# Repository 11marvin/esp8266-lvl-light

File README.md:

# ESP8266 LVL Light Control Board

This project contains the KiCad design files for a replacement control board used to control the LVL ceiling light (https://templates.blakadder.com/lvl_300.html) with additional features such as brightness adjustment, colour temperature control (CCT) and Wi-Fi connectivity. The board also includes provisions for connecting an I2C bus, a GPIO and power supply (3V3, GND).

## Features

- Control LVL ceiling light using ESP8266-12F
- Adjust brightness and color temperature (CCT)
- Wi-Fi connectivity for remote control and automation
- I2C bus and GPIO for additional device integration

## Board

32 mm x 20 mm (without antenna overlap)

### Front

### Back

## Contributing

Contributions are welcome! If you find any issues or have suggestions for improvements, please open an issue or submit a pull request.

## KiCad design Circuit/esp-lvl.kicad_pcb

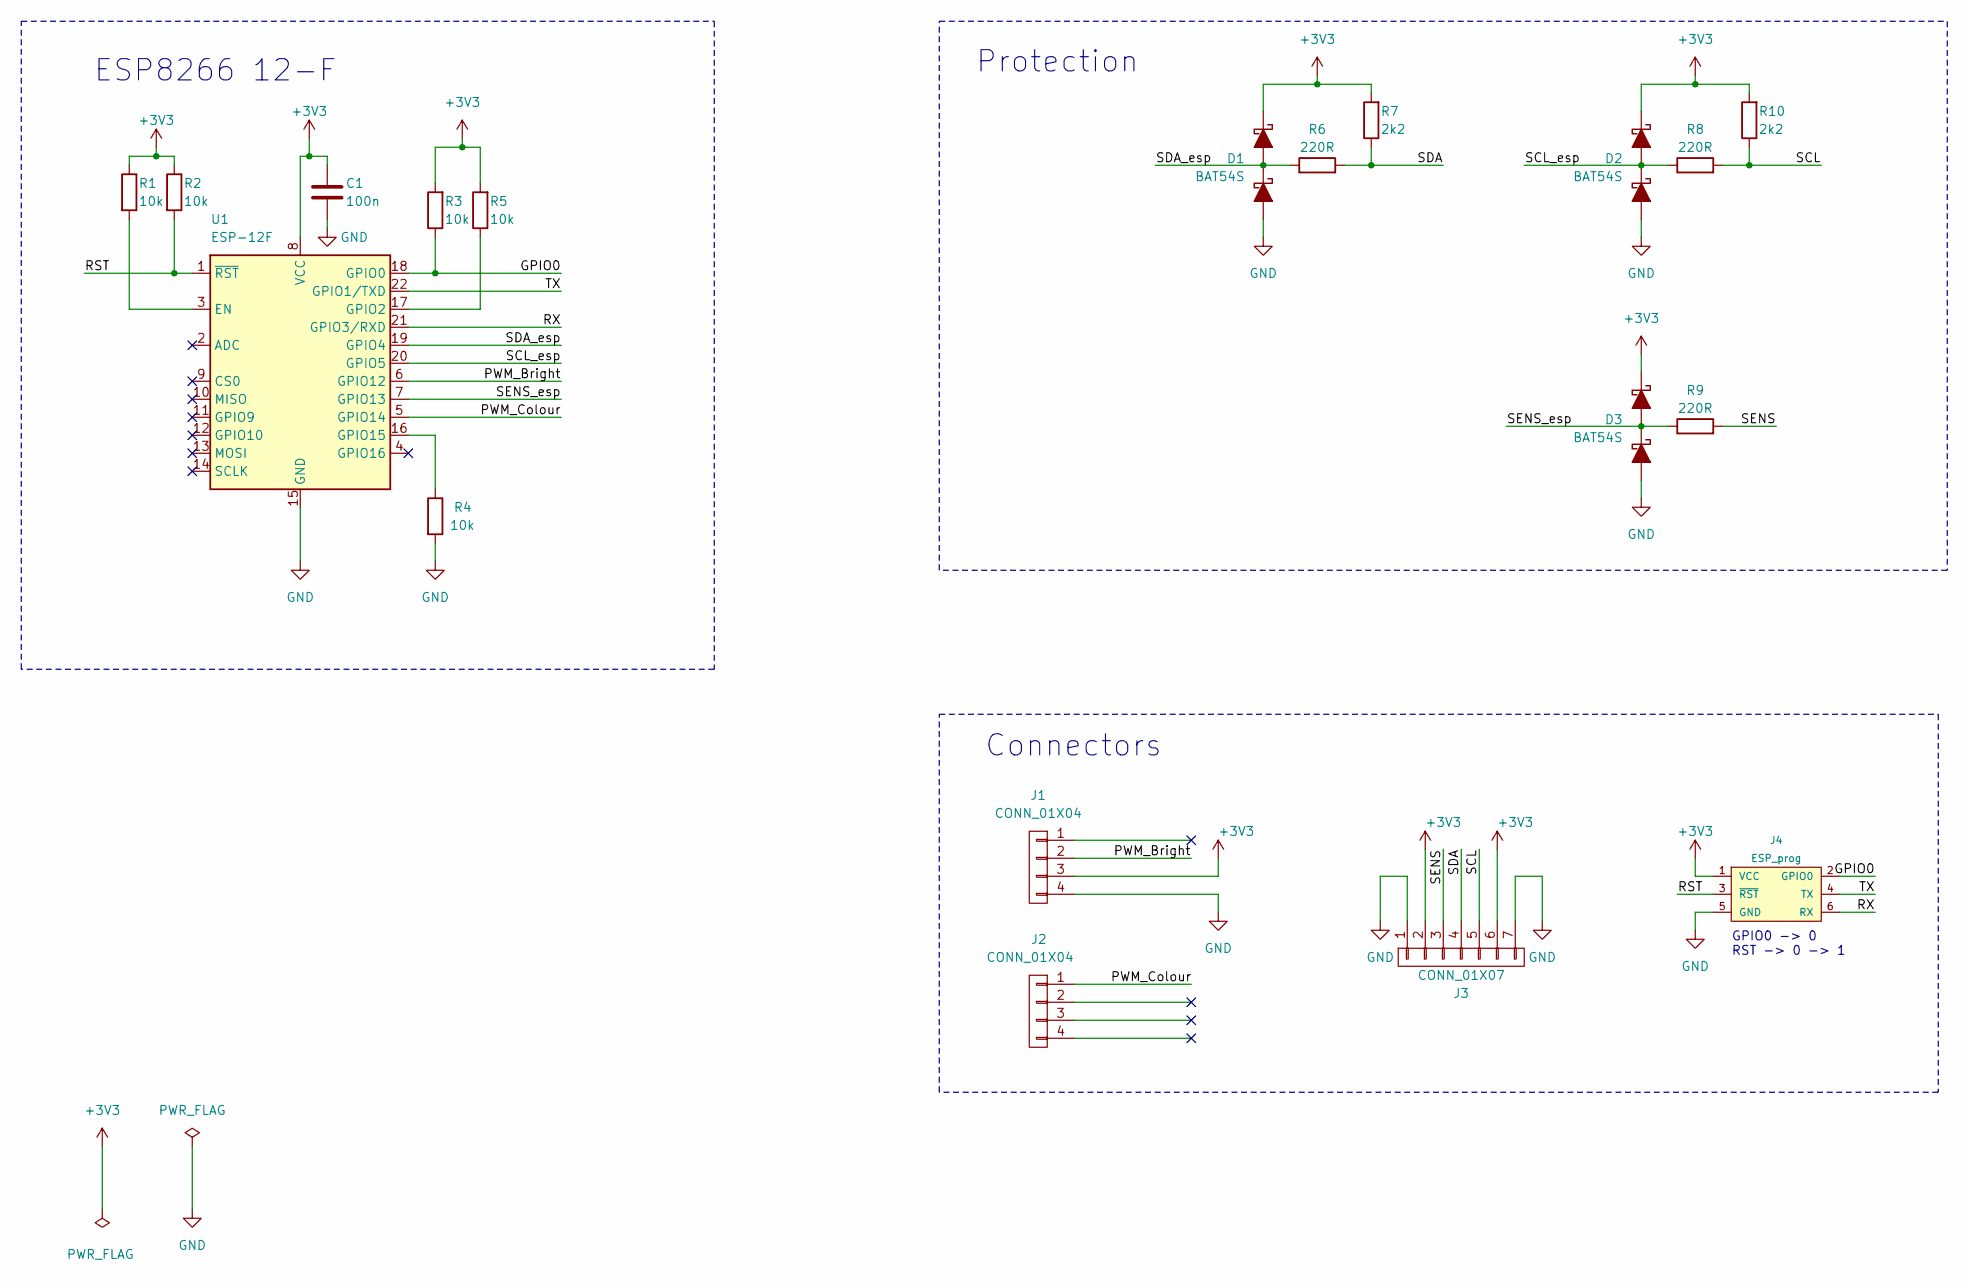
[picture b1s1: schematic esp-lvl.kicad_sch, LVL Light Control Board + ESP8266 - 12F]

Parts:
C1: 100n; C_0603_1608Metric
D1, D2, D3: BAT54S; SOT-23
J1, J2: CONN_01X04; PinHeader_1x04_P2.54mm_Vertical
J3: CONN_01X07; PinHeader_1x07_P2.54mm_Vertical
J4: ESP_prog; Tag-Connect_TC2030-IDC-NL
R1, R2, R3, R4, R5: 10k; R_0603_1608Metric
R6, R8, R9: 220R; R_0603_1608Metric
R7, R10: 2k2; R_0603_1608Metric
U1: ESP-12F; ESP-12E

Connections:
+3V3: C1.1, D1.2 (C), D2.2 (C), D3.2 (C), J1.3, J3.2, J3.6, J4.1 (VCC), R1.1, R2.1, R3.2, R5.2, R7.2, R10.2, U1.8 (VCC)
/GPIO0: J4.2 (GPIO0), R3.1, U1.18 (GPIO0)
/PWM_Bright: J1.2, U1.6 (GPIO12)
/PWM_Colour: J2.1, U1.5 (GPIO14)
/RST: J4.3 (~RST), R2.2, U1.1 (~RST)
/RX: J4.6 (RX), U1.21 (GPIO3/RXD)
/SCL: J3.5, R8.2, R10.1
/SCL_esp: D2.3 (C), R8.1, U1.20 (GPIO5)
/SDA: J3.4, R6.2, R7.1
/SDA_esp: D1.3 (C), R6.1, U1.19 (GPIO4)
/SENS: J3.3, R9.2
/SENS_esp: D3.3 (C), R9.1, U1.7 (GPIO13)
/TX: J4.4 (TX), U1.22 (GPIO1/TXD)
GND: C1.2, D1.1 (A), D2.1 (A), D3.1 (A), J1.4, J3.1, J3.7, J4.5 (GND), R4.2, U1.15 (GND)
unnamed: R1.2, U1.3 (EN)
unnamed: R5.1, U1.17 (GPIO2)
unnamed: R4.1, U1.16 (GPIO15)

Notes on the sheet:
Connectors
GPIO0 -> 0 RST -> 0 -> 1
Protection
ESP8266 12-F

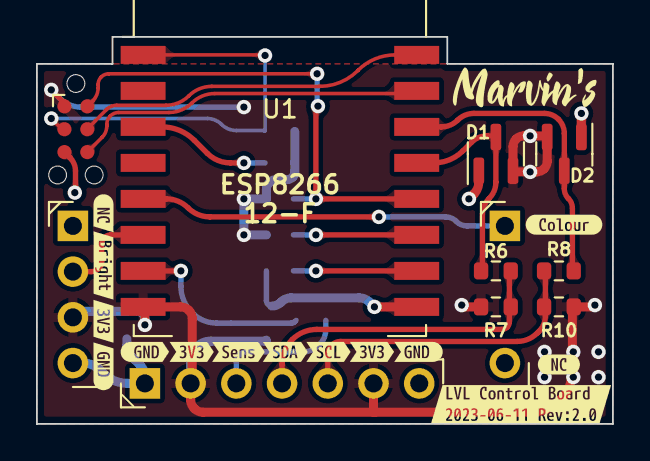
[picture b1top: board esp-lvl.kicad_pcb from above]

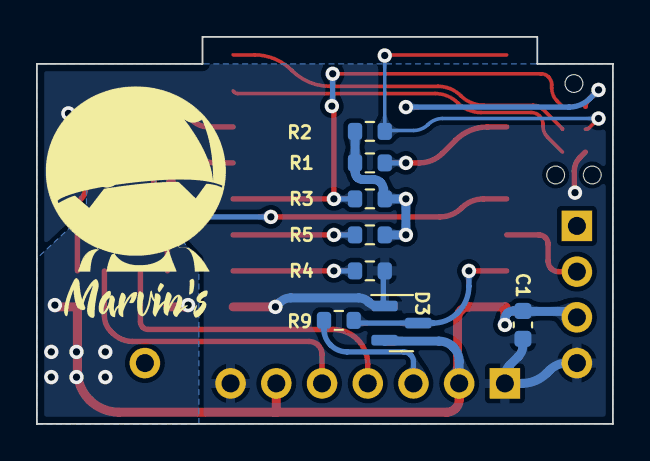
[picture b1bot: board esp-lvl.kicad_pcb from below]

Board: 2 copper layers, 32.0 x 21.5 mm, 35 parts (9 on the bottom side), 17 nets.

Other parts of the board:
kibuzzard-6485D4C1: G***; kibuzzard-6485D4C1
kibuzzard-6485EB90: G***; kibuzzard-6485EB90
kibuzzard-64859B50: G***; kibuzzard-64859B50
kibuzzard-648599E7: G***; kibuzzard-648599E7
kibuzzard-6485947F: G***; kibuzzard-6485947F
kibuzzard-6485998B: G***; kibuzzard-6485998B
kibuzzard-64859500, kibuzzard-64859500#2: G***; kibuzzard-64859500
kibuzzard-64859549: G***; kibuzzard-64859549
kibuzzard-64859551: G***; kibuzzard-64859551
kibuzzard-64859557: G***; kibuzzard-64859557
kibuzzard-64859561: G***; kibuzzard-64859561
kibuzzard-64859916: G***; kibuzzard-64859916
kibuzzard-64859921: G***; kibuzzard-64859921
kibuzzard-64859928: G***; kibuzzard-64859928
kibuzzard-64860007: G***; kibuzzard-64860007

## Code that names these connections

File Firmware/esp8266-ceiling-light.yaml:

substitutions:
  devicename: "ceiling-light"
  friendly_name: "Ceiling Light"

esphome:
  platform: ESP8266
  board: esp12e

  name: ${devicename}
  friendly_name: ${friendly_name}
  name_add_mac_suffix: True

  comment: Dimmable ceiling light with CCT and motion detector.
  project:
    name: Marvin's.${friendly_name}
    version: "1.0.3"

  on_boot:
    - script.execute: offline_light

dashboard_import:
  package_import_url: github://11marvin/esp8266-lvl-light/Firmware/esp8266-ceiling-light.yaml@master

wifi:

  # Enable fallback hotspot (captive portal) in case wifi connection fails
  ap: {} # This spawns an AP with the device name and mac address with no password.

web_server:
  port: 80
  
captive_portal:

# Enable logging
logger:

# Enable Home Assistant API
api:

# Enable Home Assistant OTA
ota:
  platform: esphome


script:
  - id: offline_light
    mode: restart     # Light will be kept on during 10 minutes since
                      # the latest time the script is executed
    then:
      - light.turn_on:
          id: mylight 
          brightness: 90%
          color_temperature: 3900K
      - delay: 10 min
      - light.turn_off: mylight

sensor:
  - platform: wifi_signal
    name: WiFi Signal
    update_interval: 60s

binary_sensor:
  - platform: gpio
    id: motion
    pin:
      number: GPIO13
    name: motion
    device_class: motion
    on_press:
      - while:
          condition:
            binary_sensor.is_on: motion
          then:
            - if:
                condition:
                  not:
                    api.connected:
                then:
                  - script.execute: offline_light
            - delay: 1 min

switch:
  - platform: restart
    name: Restart
    
light:
  - platform: color_temperature
    id: mylight
    name: "Light"
    brightness: output_brightness
    color_temperature: output_temperature
    cold_white_color_temperature: 4600 K
    warm_white_color_temperature: 2800 K

  - platform: monochromatic
    name: "Notification LED"
    output: output_component1
    id: led
    
output:
  - platform: esp8266_pwm
    id: output_component1
    pin: GPIO2
    inverted: True
    
  - platform: esp8266_pwm
    id: output_brightness
    min_power: 0.06
    zero_means_zero: True
    pin: GPIO12
    inverted: False
    
  - platform: esp8266_pwm
    id: output_temperature
    pin: GPIO14
    inverted: True

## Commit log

2023-06-10 Init
2023-06-10 README
2023-06-10 Files structure
2023-06-10 Docs
2023-06-28 v2.0
2023-07-18 BOM updated
2023-07-18 gitignore
2023-07-18 add models for 3D printing of stencils
2024-04-27 add FW
2024-04-28 FW 1.0.1
2025-02-02 add OTA platform: esphome
2025-02-02 Removed debug settings for temperature and brightness
2025-02-02 version
